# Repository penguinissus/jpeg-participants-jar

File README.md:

# jpeg-participants-jar
hackathon souvenir
# Bill of Materials (per individual pcb)
1 led  
2 resistor (220 ohm)  
1 npn transistor  
1 battery holder  
1 push button

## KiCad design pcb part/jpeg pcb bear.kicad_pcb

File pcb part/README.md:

# PCB Part
It is a pcb which acts as cover for jar  
Has a constantly on light facing the inside of the jar so the jar looks like its glowing  
Button is on the outside of the jar cover connected to a not gate  
when button is pressed, light turns off  
# Bill of Materials (per individual pcb)
1 led  
2 resistor (220 ohm)  
1 npn transistor  
1 battery holder  
1 push button

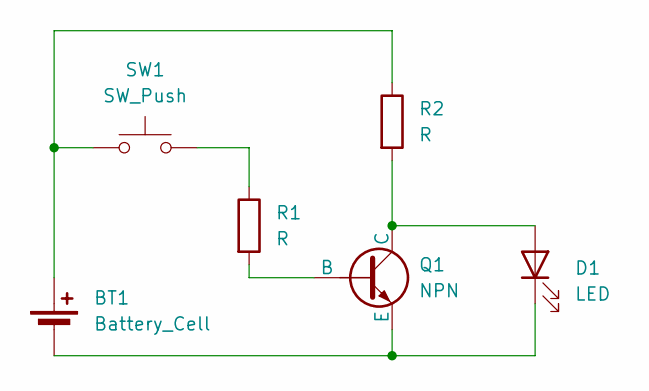
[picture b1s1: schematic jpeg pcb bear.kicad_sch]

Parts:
BT1: Battery_Cell; BatteryHolder_Keystone_3034_1x20mm
D1: LED; LED_D5.0mm
Q1: NPN; TO-92L_HandSolder
R1, R2: R; R_Axial_DIN0207_L6.3mm_D2.5mm_P7.62mm_Horizontal
SW1: SW_Push; SW_PUSH_6mm

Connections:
unnamed: BT1.1 (+), R2.1, SW1.1
unnamed: BT1.2 (-), D1.1 (K), Q1.3 (E)
unnamed: D1.2 (A), Q1.1 (C), R2.2
unnamed: Q1.2 (B), R1.2
unnamed: R1.1, SW1.2

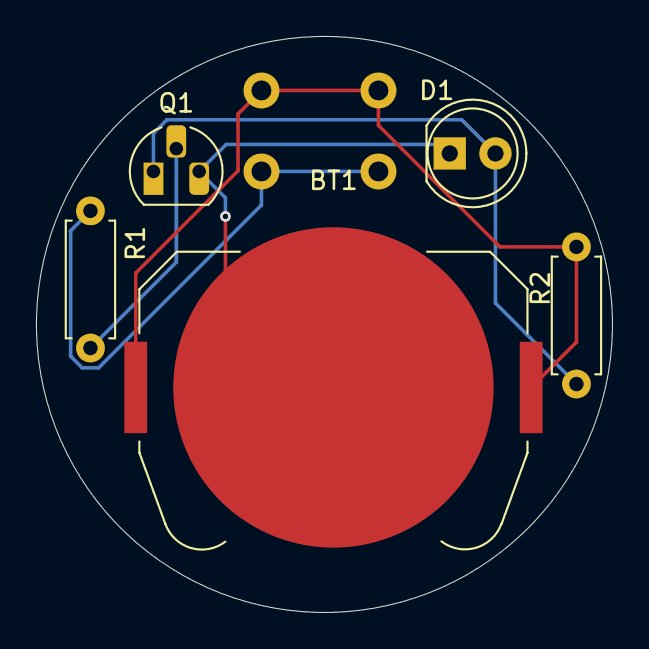
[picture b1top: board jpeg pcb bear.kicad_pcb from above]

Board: 2 copper layers, 32.0 x 32.0 mm, 6 parts (1 on the bottom side), 5 nets.
